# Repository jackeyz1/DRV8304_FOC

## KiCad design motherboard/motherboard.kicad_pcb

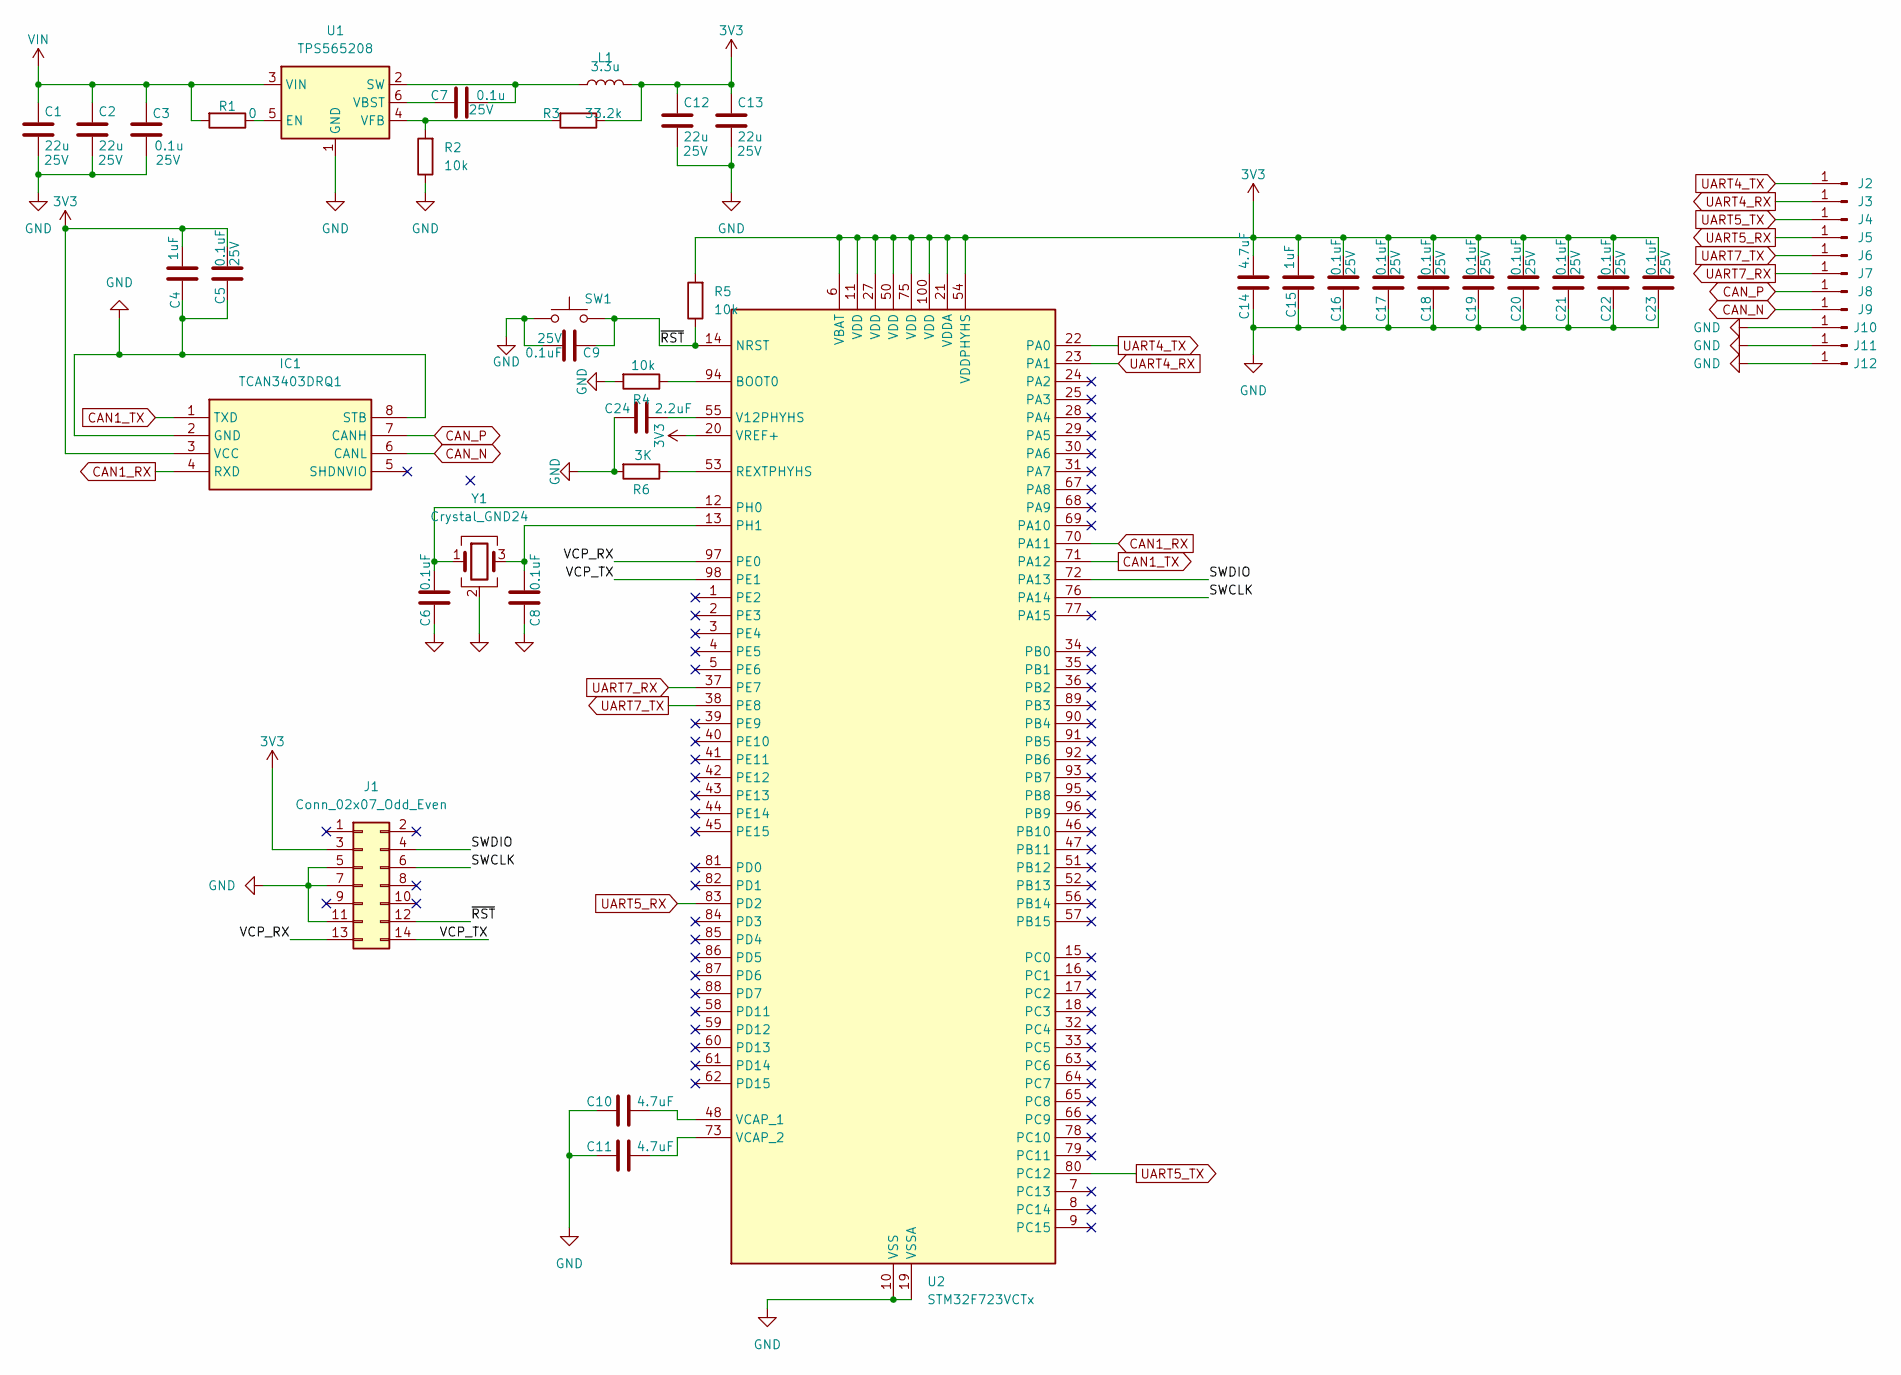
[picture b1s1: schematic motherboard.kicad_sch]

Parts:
C1, C2, C12, C13: 22u; C_0805_2012Metric; Voltage Rating 25V
C3, C7: 0.1u; C_0402_1005Metric; Voltage Rating 25V
C4, C15: 1uF; C_0603_1608Metric
C5, C9, C16, C17, C18, C19, C20, C21, C22, C23: 0.1uF; C_0402_1005Metric; Voltage Rating 25V
C6, C8: 0.1uF; C_0402_1005Metric
C10, C11, C14: 4.7uF; C_0603_1608Metric
C24: 2.2uF; C_0603_1608Metric
IC1: TCAN3403DRQ1; SOIC-8_3.9x4.9mm_P1.27mm; Mouser Part Number 595-TCAN3403DRQ1
J1: Conn_02x07_Odd_Even; PinHeader_2x07_P1.27mm_Vertical_SMD
J2, J3, J4, J5, J6, J7, J8, J9, J10, J11, J12: Conn_01x01_Pin; SolderWire-1sqmm_1x01_D1.4mm_OD2.7mm
L1: 3.3u; L_APV_APH0420
R1: 0; R_0201_0603Metric
R2: 10k; R_0201_0603Metric
R3: 33.2k; R_0201_0603Metric
R4, R5: 10k; R_0402_1005Metric
R6: 3K; R_0402_1005Metric
SW1: SW_Push; SW_SPST_B3U-1000P-B
U1: TPS565208; SOT-23-6
U2: STM32F723VCTx; LQFP-100_14x14mm_P0.5mm
Y1: Crystal_GND24; Crystal_SMD_2016-4Pin_2.0x1.6mm

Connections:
3V3: C4.1, C5.2, C12.1, C13.1, C14.1, C15.1, C16.2, C17.2, C18.2, C19.2, C20.2, C21.2, C22.2, C23.2, IC1.3 (VCC), J1.3, L1.2, R3.1, R5.2, U2.6 (VBAT), U2.11 (VDD), U2.20 (VREF+), U2.21 (VDDA), U2.27 (VDD), U2.50 (VDD), U2.54 (VDDPHYHS), U2.75 (VDD), U2.100 (VDD)
/SWCLK: J1.6, U2.76 (PA14)
/SWDIO: J1.4, U2.72 (PA13)
/VCP_RX: J1.13, U2.97 (PE0)
/VCP_TX: J1.14, U2.98 (PE1)
/~RST: C9.1, J1.12, R5.1, SW1.2, U2.14 (NRST)
CAN1_RX: IC1.4 (RXD), U2.70 (PA11)
CAN1_TX: IC1.1 (TXD), U2.71 (PA12)
CAN_N: IC1.6 (CANL), J9.1 (Pin_1_1)
CAN_P: IC1.7 (CANH), J8.1 (Pin_1_1)
GND: C1.2, C2.2, C3.2, C4.2, C5.1, C6.1, C8.1, C9.2, C10.2, C11.2, C12.2, C13.2, C14.2, C15.2, C16.1, C17.1, C18.1, C19.1, C20.1, C21.1, C22.1, C23.1, C24.2, IC1.2 (GND), IC1.8 (STB), J1.5, J1.7, J1.11, J10.1 (Pin_1_1), J11.1 (Pin_1_1), J12.1 (Pin_1_1), R2.1, R4.2, R6.2, SW1.1, U1.1 (GND), U2.10 (VSS), U2.19 (VSSA), U2.26 (VSS), U2.49 (VSS), U2.74 (VSS), U2.99 (VSS), Y1.2 (G), Y1.4 (G)
unnamed: R1.1, U1.5 (EN)
unnamed: C7.2, L1.1, U1.2 (SW)
unnamed: C7.1, U1.6 (VBST)
unnamed: R2.2, R3.2, U1.4 (VFB)
unnamed: R4.1, U2.94 (BOOT0)
unnamed: C6.2, U2.12 (PH0), Y1.1
unnamed: C8.2, U2.13 (PH1), Y1.3
unnamed: R6.1, U2.53 (REXTPHYHS)
unnamed: C24.1, U2.55 (V12PHYHS)
unnamed: C10.1, U2.48 (VCAP_1)
unnamed: C11.1, U2.73 (VCAP_2)
UART4_RX: J3.1 (Pin_1_1), U2.23 (PA1); also elsewhere on the board
UART4_TX: J2.1 (Pin_1_1), U2.22 (PA0); also elsewhere on the board
UART5_RX: J5.1 (Pin_1_1), U2.83 (PD2)
UART5_TX: J4.1 (Pin_1_1), U2.80 (PC12)
UART7_RX: J7.1 (Pin_1_1), U2.37 (PE7)
UART7_TX: J6.1 (Pin_1_1), U2.38 (PE8)
VIN: C1.1, C2.1, C3.1, R1.2, U1.3 (VIN)

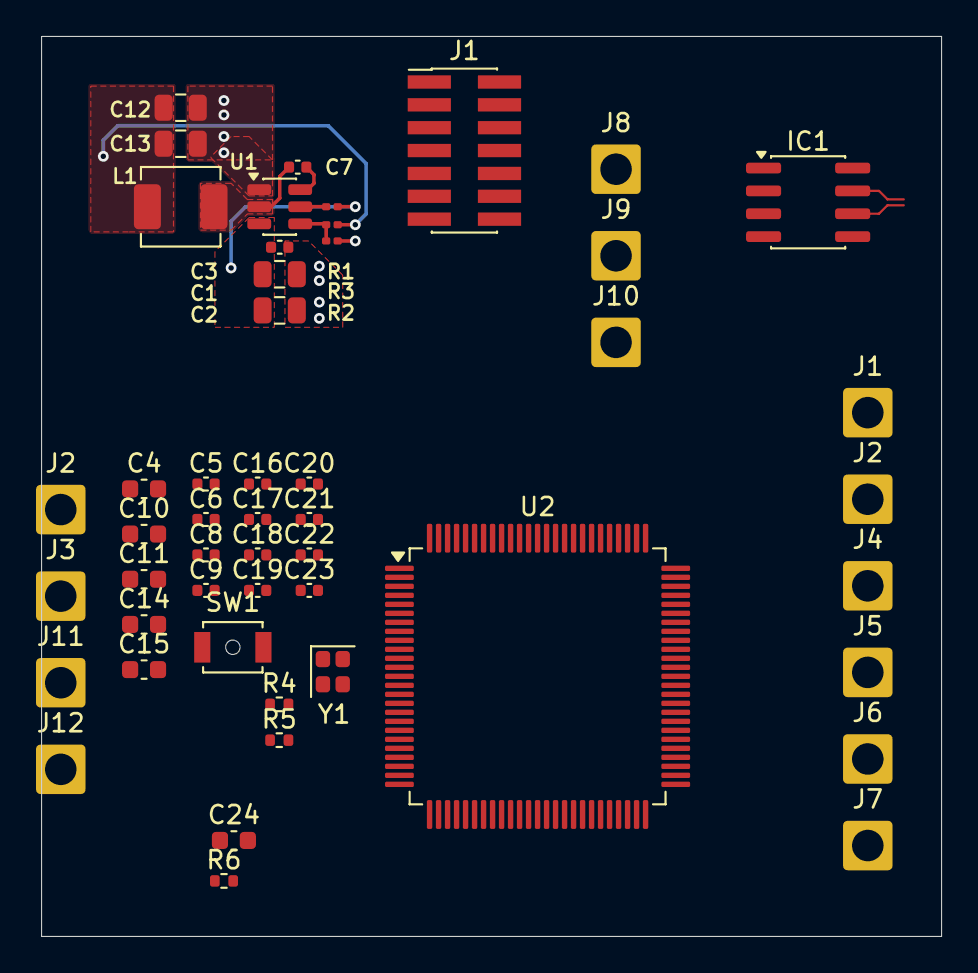
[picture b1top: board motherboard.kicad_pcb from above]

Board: 4 copper layers, 50.0 x 50.0 mm, 50 parts (0 on the bottom side), 29 nets.

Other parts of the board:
J1#2, J2#2: Conn_01x01_Pin; SolderWire-1sqmm_1x01_D1.4mm_OD2.7mm

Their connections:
UART4_RX: J1#2.1 (Pin_1_1); also elsewhere on the board
UART4_TX: J2#2.1 (Pin_1_1); also elsewhere on the board

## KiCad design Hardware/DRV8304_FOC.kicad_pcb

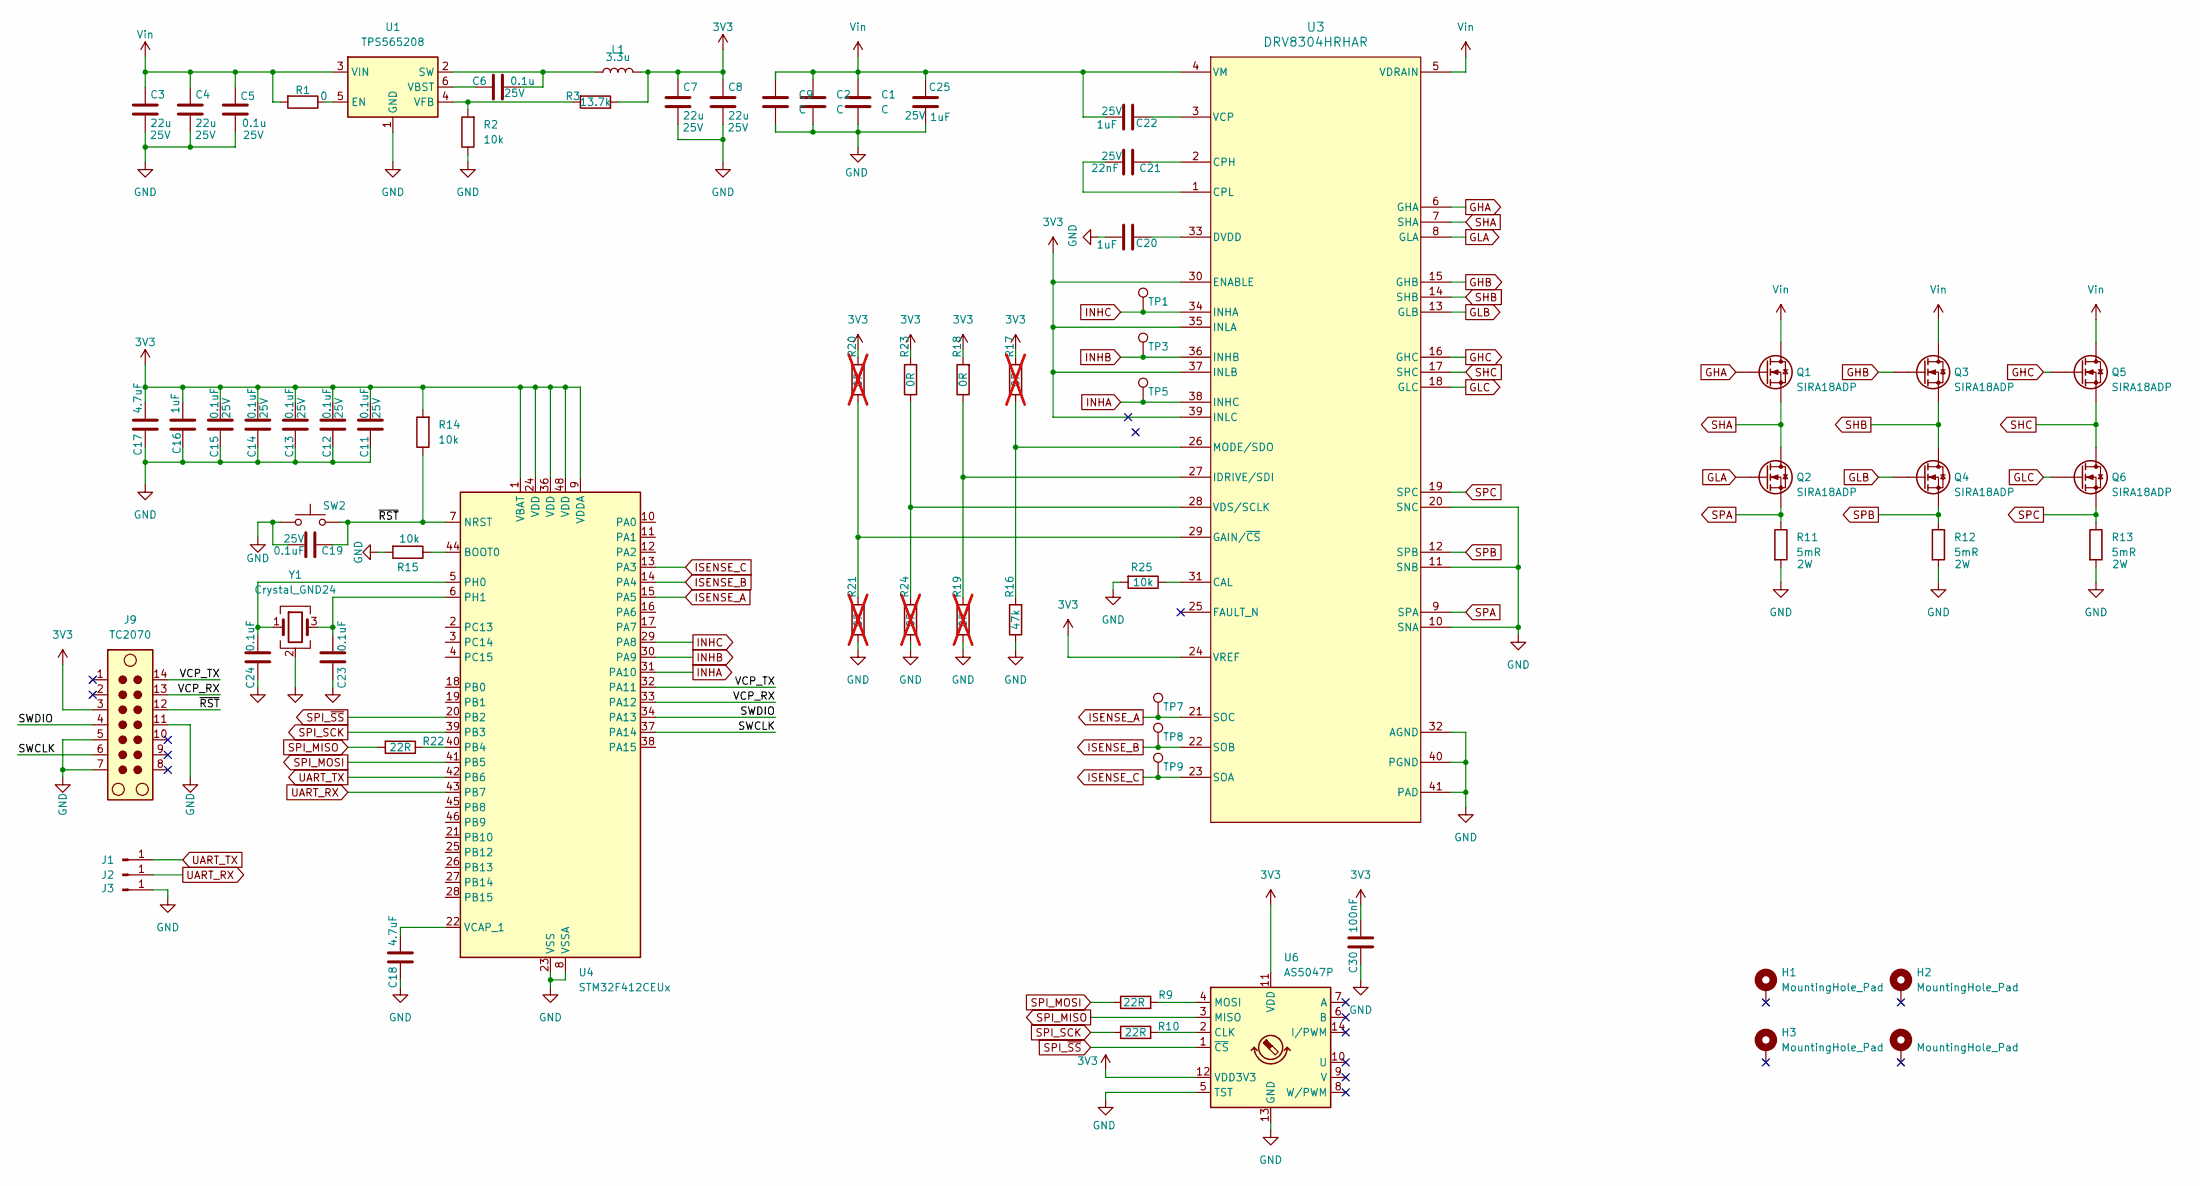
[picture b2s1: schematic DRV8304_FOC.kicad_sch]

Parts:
C1, C2, C9: C; C_1206_3216Metric
C3, C4, C7, C8: 22u; C_0805_2012Metric; Voltage Rating 25V
C5, C6: 0.1u; C_0402_1005Metric; Voltage Rating 25V
C11, C12, C13, C14, C15, C19: 0.1uF; C_0402_1005Metric; Voltage Rating 25V
C16, C20: 1uF; C_0603_1608Metric
C17, C18: 4.7uF; C_0603_1608Metric
C21: 22nF; C_0402_1005Metric; Voltage Rating 25V
C22, C25: 1uF; C_0603_1608Metric; Voltage Rating 25V
C23, C24: 0.1uF; C_0402_1005Metric
C30: 100nF; C_0402_1005Metric
H1, H2, H3, H4: MountingHole_Pad; MountingHole_3.2mm_M3_ISO14580_Pad_TopOnly
J1, J2, J3: Conn_01x01_Pin; SolderWirePad_1x01_SMD_1x2mm
J9: TC2070; Tag-Connect_TC2070-IDC-FP_2x07_P1.27mm_Vertical
L1: 3.3u; L_1008_2520Metric
Q1, Q2, Q3, Q4, Q5, Q6: SIRA18ADP; PowerPAK_SO-8_Single
R1: 0; R_0402_1005Metric
R2, R14, R15, R25: 10k; R_0402_1005Metric
R3: 13.7k; R_0402_1005Metric
R9, R10, R22: 22R; R_0402_1005Metric
R11, R12, R13: 5mR; R_1210_3225Metric; Voltage Rating 2W
R16: 47k; R_0402_1005Metric
R17, R19, R20, R21, R24: 0R; R_0402_1005Metric; not fitted
R18, R23: 0R; R_0402_1005Metric
SW2: SW_Push; SW_SPST_B3U-1000P-B
TP1, TP3, TP5, TP7, TP8, TP9: TestPoint; TestPoint_1mm
U1: TPS565208; SOT-23-6
U3: DRV8304HRHAR; RHA0040E
U4: STM32F412CEUx; QFN-48-1EP_7x7mm_P0.5mm_EP5.6x5.6mm
U6: AS5047P; TSSOP-14_4.4x5mm_P0.65mm
Y1: Crystal_GND24; Crystal_SMD_2016-4Pin_2.0x1.6mm

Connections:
3V3: C7.1, C8.1, C11.2, C12.2, C13.2, C14.2, C15.2, C16.1, C17.1, C30.1, J9.3, L1.2, R3.1, R14.2, R17.2, R18.2, R20.2, R23.2, U3.24 (VREF), U3.30 (ENABLE), U3.35 (INLA), U3.37 (INLB), U3.39 (INLC), U4.1 (VBAT), U4.9 (VDDA), U4.24 (VDD), U4.36 (VDD), U4.48 (VDD), U6.11 (VDD), U6.12 (VDD3V3)
/SWCLK: J9.6, U4.37 (PA14)
/SWDIO: J9.4, U4.34 (PA13)
/VCP_RX: J9.13, U4.33 (PA12)
/VCP_TX: J9.14, U4.32 (PA11)
/~RST: C19.1, J9.12, R14.1, SW2.2, U4.7 (NRST)
GHA: Q1.4 (G), U3.6 (GHA)
GHB: Q3.4 (G), U3.15 (GHB)
GHC: Q5.4 (G), U3.16 (GHC)
GLA: Q2.4 (G), U3.8 (GLA)
GLB: Q4.4 (G), U3.13 (GLB)
GLC: Q6.4 (G), U3.18 (GLC)
GND: C1.2, C2.2, C3.2, C4.2, C5.2, C7.2, C8.2, C9.2, C11.1, C12.1, C13.1, C14.1, C15.1, C16.2, C17.2, C18.2, C19.2, C20.1, C23.1, C24.1, C25.1, C30.2, J3.1 (Pin_1_1), J9.5, J9.7, J9.11, R2.1, R11.2, R12.2, R13.2, R15.2, R16.1, R19.1, R21.1, R24.1, R25.2, SW2.1, U1.1 (GND), U3.10 (SNA), U3.11 (SNB), U3.20 (SNC), U3.32 (AGND), U3.40 (PGND), U3.41 (PAD), U3.V, U4.8 (VSSA), U4.23 (VSS), U4.35 (VSS), U4.47 (VSS), U4.49 (VSS), U6.5 (TST), U6.13 (GND), Y1.2 (G), Y1.4 (G)
INHA: TP5.1 (1_1), U3.38 (INHC), U4.31 (PA10)
INHB: TP3.1 (1_1), U3.36 (INHB), U4.30 (PA9)
INHC: TP1.1 (1_1), U3.34 (INHA), U4.29 (PA8)
ISENSE_A: TP7.1 (1_1), U3.21 (SOC), U4.15 (PA5)
ISENSE_B: TP8.1 (1_1), U3.22 (SOB), U4.14 (PA4)
ISENSE_C: TP9.1 (1_1), U3.23 (SOA), U4.13 (PA3)
unnamed: R1.1, U1.5 (EN)
unnamed: C6.2, L1.1, U1.2 (SW)
unnamed: C6.1, U1.6 (VBST)
unnamed: R2.2, R3.2, U1.4 (VFB)
unnamed: R25.1, U3.31 (CAL)
unnamed: C21.1, U3.2 (CPH)
unnamed: C21.2, U3.1 (CPL)
unnamed: C20.2, U3.33 (DVDD)
unnamed: R20.1, R21.2, U3.29 (GAIN/~CS)
unnamed: R18.1, R19.2, U3.27 (IDRIVE/SDI)
unnamed: R16.2, R17.1, U3.26 (MODE/SDO)
unnamed: C22.2, U3.3 (VCP)
unnamed: R23.1, R24.2, U3.28 (VDS/SCLK)
unnamed: R15.1, U4.44 (BOOT0)
unnamed: R22.1, U4.40 (PB4)
unnamed: C24.2, U4.5 (PH0), Y1.1
unnamed: C23.2, U4.6 (PH1), Y1.3
unnamed: C18.1, U4.22 (VCAP_1)
unnamed: R10.2, U6.2 (CLK)
unnamed: R9.2, U6.4 (MOSI)
SHA: Q1.1 (S), Q1.2 (S), Q1.3 (S), Q2.5 (D), U3.7 (SHA)
SHB: Q3.1 (S), Q3.2 (S), Q3.3 (S), Q4.5 (D), U3.14 (SHB)
SHC: Q5.1 (S), Q5.2 (S), Q5.3 (S), Q6.5 (D), U3.17 (SHC)
SPA: Q2.1 (S), Q2.2 (S), Q2.3 (S), R11.1, U3.9 (SPA)
SPB: Q4.1 (S), Q4.2 (S), Q4.3 (S), R12.1, U3.12 (SPB)
SPC: Q6.1 (S), Q6.2 (S), Q6.3 (S), R13.1, U3.19 (SPC)
SPI_MISO: R22.2, U6.3 (MISO)
SPI_MOSI: R9.1, U4.41 (PB5)
SPI_SCK: R10.1, U4.39 (PB3)
SPI_~SS: U4.20 (PB2), U6.1 (~CS)
UART_RX: J2.1 (Pin_1_1), U4.43 (PB7)
UART_TX: J1.1 (Pin_1_1), U4.42 (PB6)
Vin: C1.1, C2.1, C3.1, C4.1, C5.1, C9.1, C22.1, C25.2, Q1.5 (D), Q3.5 (D), Q5.5 (D), R1.2, U1.3 (VIN), U3.4 (VM), U3.5 (VDRAIN)

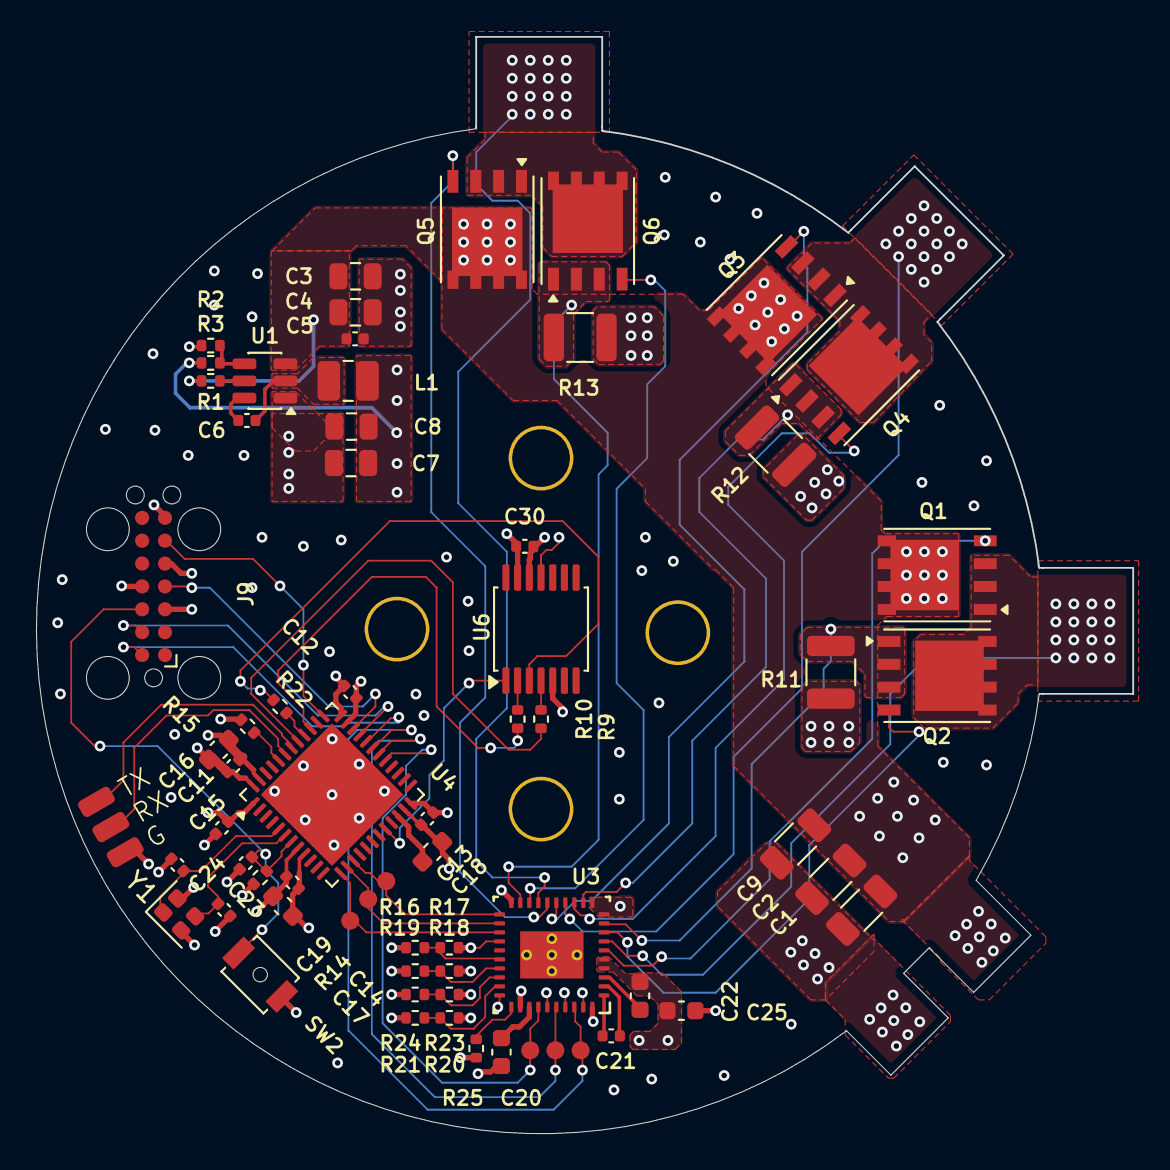
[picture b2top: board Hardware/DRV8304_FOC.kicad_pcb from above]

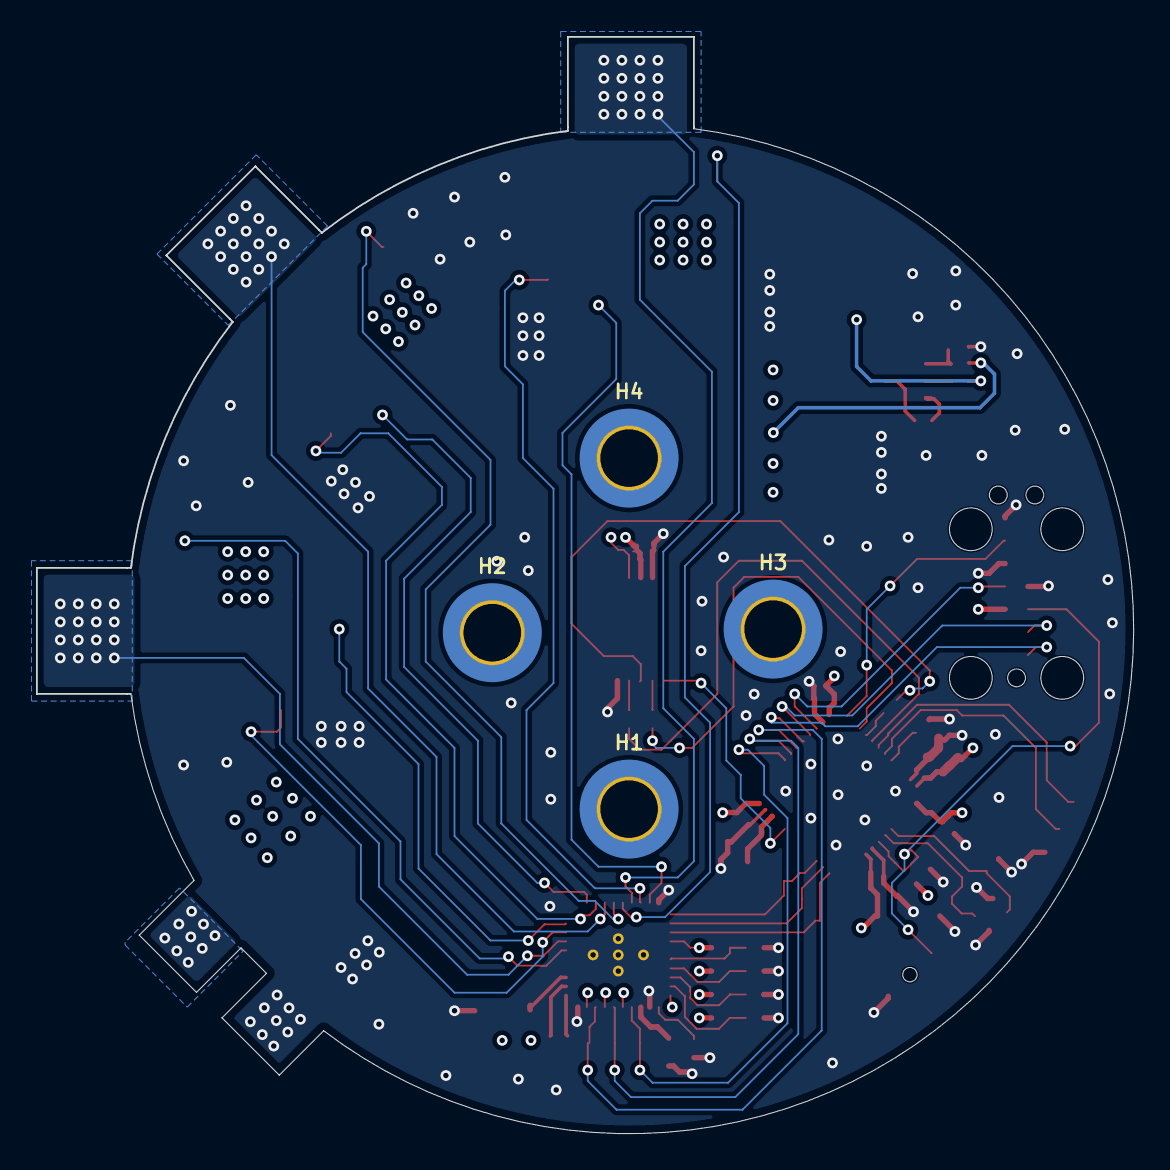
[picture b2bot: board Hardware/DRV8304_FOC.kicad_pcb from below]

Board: 4 copper layers, 60.9 x 60.9 mm, 72 parts (4 on the bottom side), 52 nets.

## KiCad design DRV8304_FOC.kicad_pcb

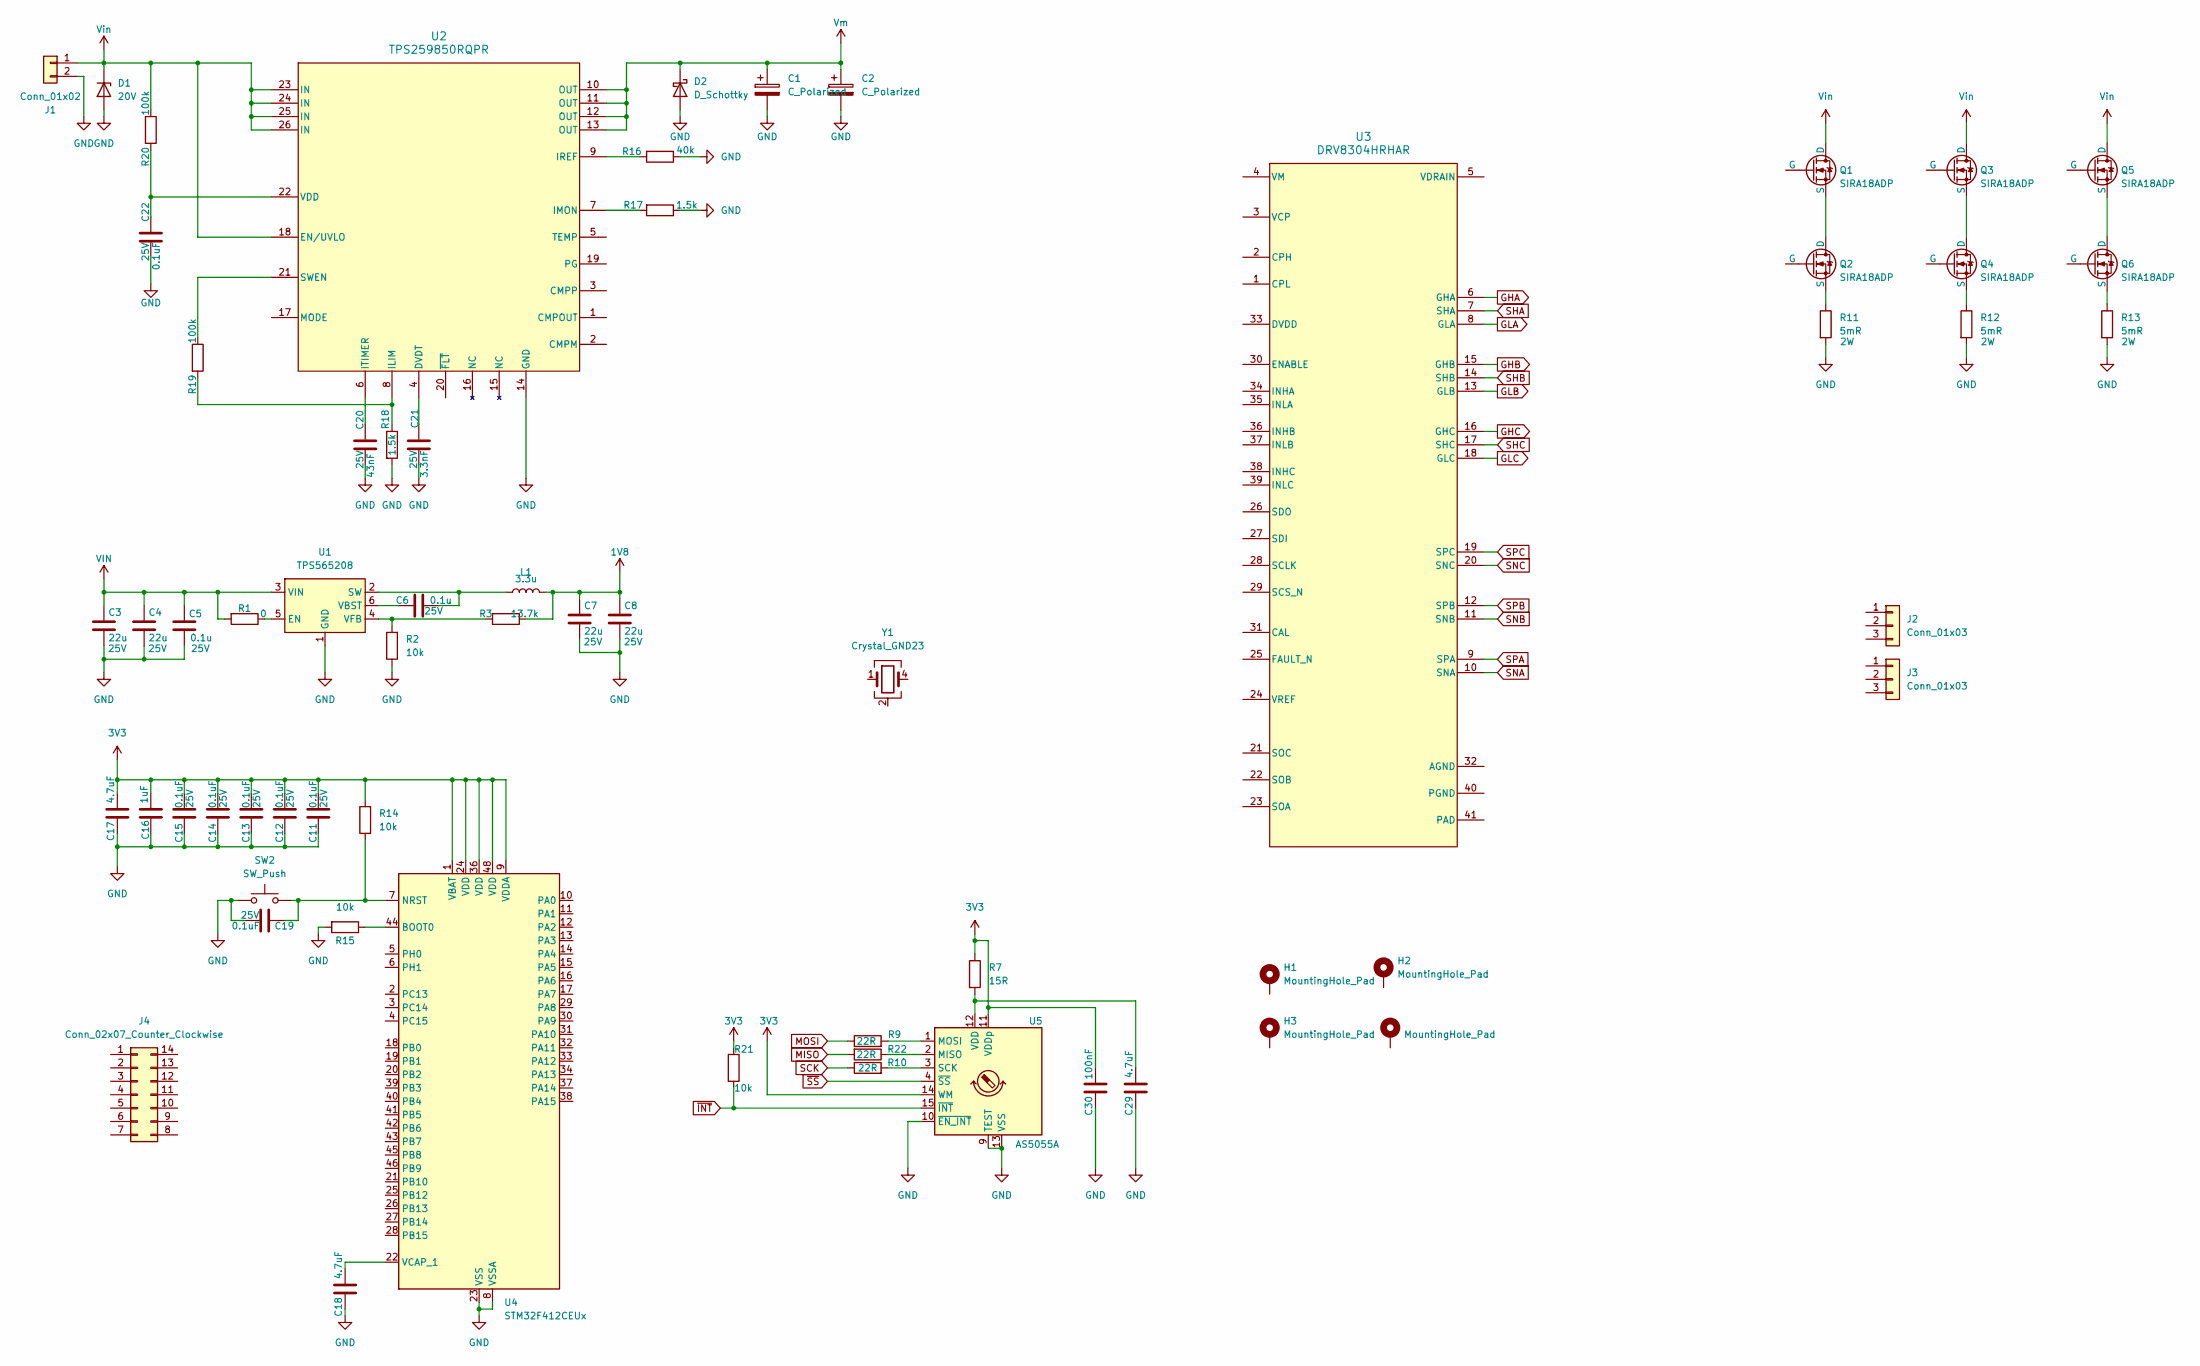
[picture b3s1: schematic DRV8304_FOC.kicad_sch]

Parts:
C1, C2: C_Polarized; CP_Elec_6.3x7.7
C3, C4, C7, C8: 22u; C_0805_2012Metric; Voltage Rating 25V
C5, C6: 0.1u; C_0402_1005Metric; Voltage Rating 25V
C11, C12, C13, C14, C15, C19, C22: 0.1uF; C_0402_1005Metric; Voltage Rating 25V
C16: 1uF; C_0603_1608Metric
C17, C18, C29: 4.7uF; C_0603_1608Metric
C20: 43nF; C_0402_1005Metric; Voltage Rating 25V
C21: 3.3nF; C_0402_1005Metric; Voltage Rating 25V
C30: 100nF; C_0402_1005Metric
D1: 20V; D_SMA
D2: D_Schottky; D_SMA
H1, H2, H3, H4: MountingHole_Pad; MountingHole_3.2mm_M3_DIN965_Pad
J1: Conn_01x02; AMASS_XT30U-M_1x02_P5.0mm_Vertical
J2: Conn_01x03; JST_XH_S3B-XH-A-1_1x03_P2.50mm_Horizontal
J3: Conn_01x03; JST_PH_S3B-PH-K_1x03_P2.00mm_Horizontal
J4: Conn_02x07_Counter_Clockwise; PinHeader_2x07_P1.27mm_Vertical_SMD
L1: 3.3u; L_1008_2520Metric
Q1, Q2, Q3, Q4, Q5, Q6: SIRA18ADP; PowerPAK_SO-8_Single
R1: 0; R_0402_1005Metric
R2, R14, R15, R21: 10k; R_0402_1005Metric
R3: 13.7k; R_0402_1005Metric
R7: 15R; R_0402_1005Metric
R9, R10, R22: 22R; R_0402_1005Metric
R11, R12, R13: 5mR; R_1210_3225Metric; Voltage Rating 2W
R16: 40k; R_0402_1005Metric
R17, R18: 1.5k; R_0402_1005Metric
R19, R20: 100k; R_0402_1005Metric
SW2: SW_Push; SW_SPST_B3U-1000P-B
U1: TPS565208; SOT-23-6
U2: TPS259850RQPR; RQP0026A-MFG
U3: DRV8304HRHAR; RHA0040E
U4: STM32F412CEUx; QFN-48-1EP_7x7mm_P0.5mm_EP5.6x5.6mm
U5: AS5055A; QFN-16-1EP_4x4mm_P0.65mm_EP2.7x2.7mm
Y1: Crystal_GND23; Crystal_SMD_2016-4Pin_2.0x1.6mm

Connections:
1V8: C7.1, C8.1, L1.2, R3.1
3V3: C11.2, C12.2, C13.2, C14.2, C15.2, C16.1, C17.1, C30.1, R7.1, R14.2, R21.1, U4.1 (VBAT), U4.9 (VDDA), U4.24 (VDD), U4.36 (VDD), U4.48 (VDD), U5.11 (VDDp), U5.14 (WM)
GHA: U3.6 (GHA)
GHB: U3.15 (GHB)
GHC: U3.16 (GHC)
GLA: U3.8 (GLA)
GLB: U3.13 (GLB)
GLC: U3.18 (GLC)
GND: C1.2, C2.2, C3.2, C4.2, C5.2, C7.2, C8.2, C11.1, C12.1, C13.1, C14.1, C15.1, C16.2, C17.2, C18.2, C19.2, C20.2, C21.2, C22.2, C29.2, C30.2, D1.2 (A), D2.2 (A), J1.2, R2.1, R11.2, R12.2, R13.2, R15.2, R16.1, R17.1, R18.2, SW2.1, U1.1 (GND), U2.14 (GND), U4.8 (VSSA), U4.23 (VSS), U4.35 (VSS), U4.47 (VSS), U4.49 (VSS), U5.9 (TEST), U5.10 (~EN_INT), U5.13 (VSS)
MISO: R22.2
MOSI: R9.1
unnamed: Q1.3 (S), Q2.1 (D)
unnamed: Q2.3 (S), R11.1
unnamed: Q3.3 (S), Q4.1 (D)
unnamed: Q4.3 (S), R12.1
unnamed: Q5.3 (S), Q6.1 (D)
unnamed: Q6.3 (S), R13.1
unnamed: R1.1, U1.5 (EN)
unnamed: C6.2, L1.1, U1.2 (SW)
unnamed: C6.1, U1.6 (VBST)
unnamed: R2.2, R3.2, U1.4 (VFB)
unnamed: C21.1, U2.4 (DVDT)
unnamed: R18.1, R19.2, U2.8 (ILIM)
unnamed: R17.2, U2.7 (IMON)
unnamed: R16.2, U2.9 (IREF)
unnamed: C20.1, U2.6 (ITIMER)
unnamed: R19.1, U2.21 (SWEN)
unnamed: C22.1, R20.2, U2.22 (VDD)
unnamed: R15.1, U4.44 (BOOT0)
unnamed: C19.1, R14.1, SW2.2, U4.7 (NRST)
unnamed: C18.1, U4.22 (VCAP_1)
unnamed: R22.1, U5.2 (MISO)
unnamed: R9.2, U5.1 (MOSI)
unnamed: R10.2, U5.3 (SCK)
unnamed: C29.1, R7.2, U5.12 (VDD)
unnamed: Y1.2 (G), Y1.3 (G)
SCK: R10.1
SHA: U3.7 (SHA)
SHB: U3.14 (SHB)
SHC: U3.17 (SHC)
SNA: U3.10 (SNA)
SNB: U3.11 (SNB)
SNC: U3.20 (SNC)
SPA: U3.9 (SPA)
SPB: U3.12 (SPB)
SPC: U3.19 (SPC)
VIN: C3.1, C4.1, C5.1, R1.2, U1.3 (VIN)
Vin: D1.1 (K), J1.1, Q1.1 (D), Q3.1 (D), Q5.1 (D), R20.1, U2.18 (EN/UVLO), U2.23 (IN), U2.24 (IN), U2.25 (IN), U2.26 (IN)
Vm: C1.1, C2.1, D2.1 (K), U2.10 (OUT), U2.11 (OUT), U2.12 (OUT), U2.13 (OUT)
~INT: R21.2, U5.15 (~INT)
~SS: U5.4 (~SS)

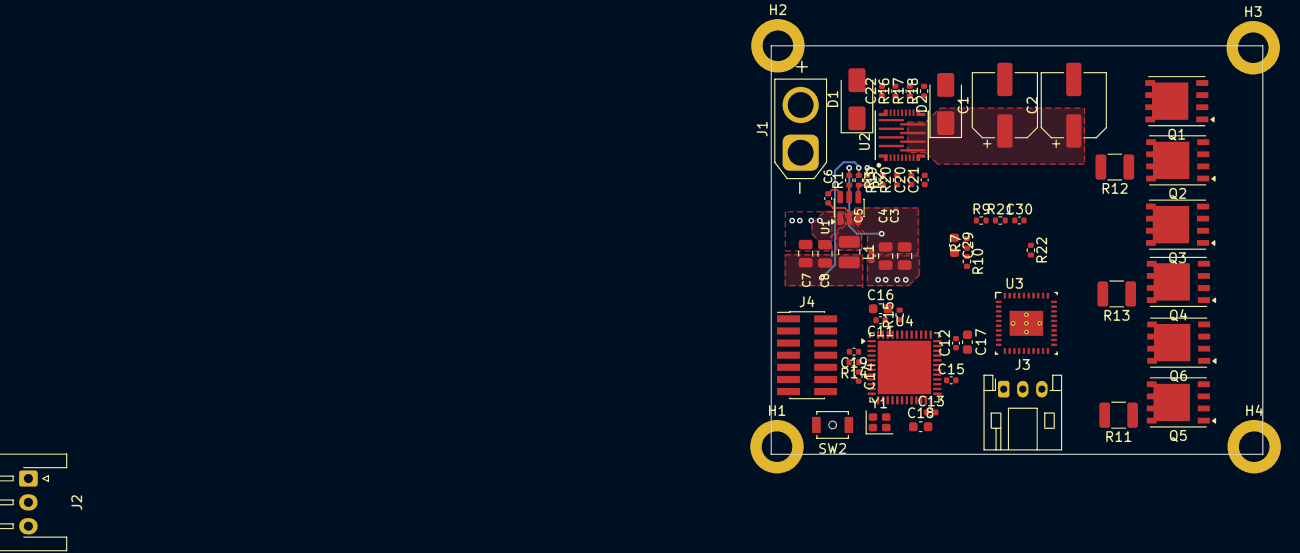
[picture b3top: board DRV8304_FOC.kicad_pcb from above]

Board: 4 copper layers, 51.5 x 42.8 mm, 64 parts (1 on the bottom side), 32 nets.

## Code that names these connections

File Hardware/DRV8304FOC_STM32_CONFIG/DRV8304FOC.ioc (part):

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Mcu.Name=STM32F412C(E-G)Ux
Mcu.Package=UFQFPN48
Mcu.UserName=STM32F412CEUx
PA10.Signal=S_TIM1_CH3
PA13.Mode=Serial_Wire
PA13.Signal=SYS_JTMS-SWDIO
PA14.Mode=Serial_Wire
PA14.Signal=SYS_JTCK-SWCLK
PA15.GPIOParameters=GPIO_Label
PA15.GPIO_Label=CS
PA15.Signal=GPIO_Output
PA3.Signal=ADCx_IN3
PA4.Signal=ADCx_IN4
PA5.Signal=ADCx_IN5
PA8.Signal=S_TIM1_CH1
PA9.Signal=S_TIM1_CH2
PB13.Mode=Output Compare1 CH1 CH1N
PB13.Signal=TIM1_CH1N
PB14.Mode=Output Compare2 CH2 CH2N
PB14.Signal=TIM1_CH2N
PB15.Mode=Output Compare3 CH3 CH3N
PB15.Signal=TIM1_CH3N
PB3.Mode=Full_Duplex_Master
PB3.Signal=SPI1_SCK
PB4.Mode=Full_Duplex_Master
PB4.Signal=SPI1_MISO
PB5.Mode=Full_Duplex_Master
PB5.Signal=SPI1_MOSI
PB6.Mode=Asynchronous
PB6.Signal=USART1_TX
PB7.Mode=Asynchronous
PB7.Signal=USART1_RX
PH0\ -\ OSC_IN.Mode=HSE-External-Oscillator
PH0\ -\ OSC_IN.Signal=RCC_OSC_IN
PH1\ -\ OSC_OUT.Mode=HSE-External-Oscillator
PH1\ -\ OSC_OUT.Signal=RCC_OSC_OUT
board=custom

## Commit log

2026-04-09 Initial KiCad project commit
2026-04-09 remove garbage
2026-04-09 clean up
2026-04-09 clean up garbage
2026-04-09 add calculation sheet
2026-04-09 hall sensor
2026-04-09 Modified encoder sch, modified layout
2026-04-13 Replace buck converter with LDO
2026-04-14 Add buck back, changed board shape, replace cer cap with alu cap
2026-04-14 Changed project structure, added STM32 config file for pinout
2026-04-16 Added Board outline DXF and test points
2026-04-27 Routing update
2026-06-13 Remove EFUSE
2026-06-13 regular commit
2026-06-14 Commit for review
2026-06-15 FAB OUT GERBER
2026-06-18 motherboard
